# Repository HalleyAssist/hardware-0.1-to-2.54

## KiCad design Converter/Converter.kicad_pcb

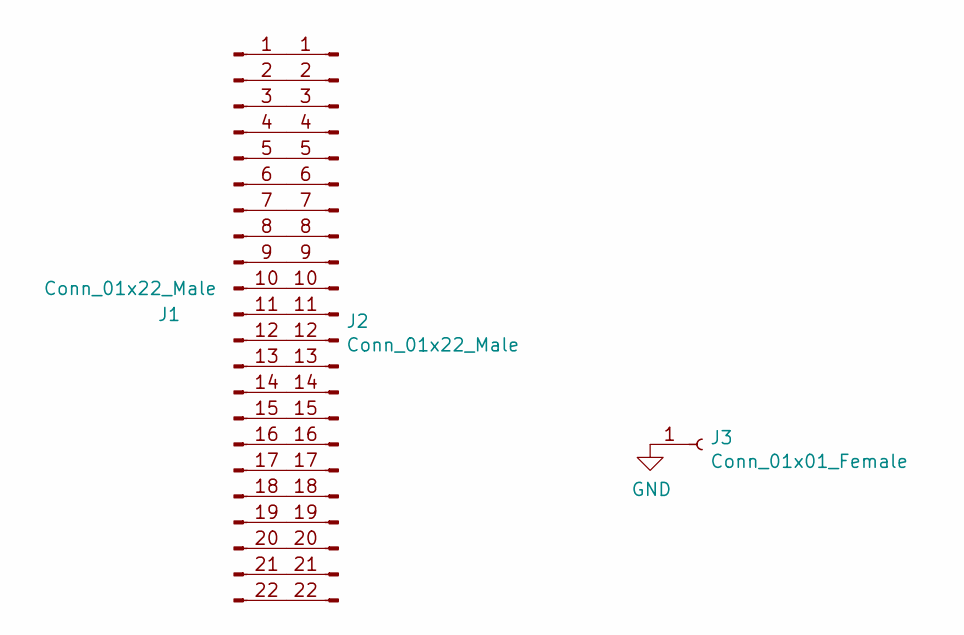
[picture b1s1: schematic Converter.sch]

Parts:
J1: Conn_01x22_Male; PinHeader_1x22_P1.00mm_Vertical
J2: Conn_01x22_Male; PinHeader_1x22_P2.54mm_Vertical
J3: Conn_01x01_Female; PinHeader_1x01_P2.54mm_Vertical

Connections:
GND: J3.1
unnamed: J1.1, J2.1
unnamed: J1.2, J2.2
unnamed: J1.3, J2.3
unnamed: J1.4, J2.4
unnamed: J1.5, J2.5
unnamed: J1.6, J2.6
unnamed: J1.7, J2.7
unnamed: J1.8, J2.8
unnamed: J1.9, J2.9
unnamed: J1.10, J2.10
unnamed: J1.11, J2.11
unnamed: J1.12, J2.12
unnamed: J1.13, J2.13
unnamed: J1.14, J2.14
unnamed: J1.15, J2.15
unnamed: J1.16, J2.16
unnamed: J1.17, J2.17
unnamed: J1.18, J2.18
unnamed: J1.19, J2.19
unnamed: J1.20, J2.20
unnamed: J1.21, J2.21
unnamed: J1.22, J2.22

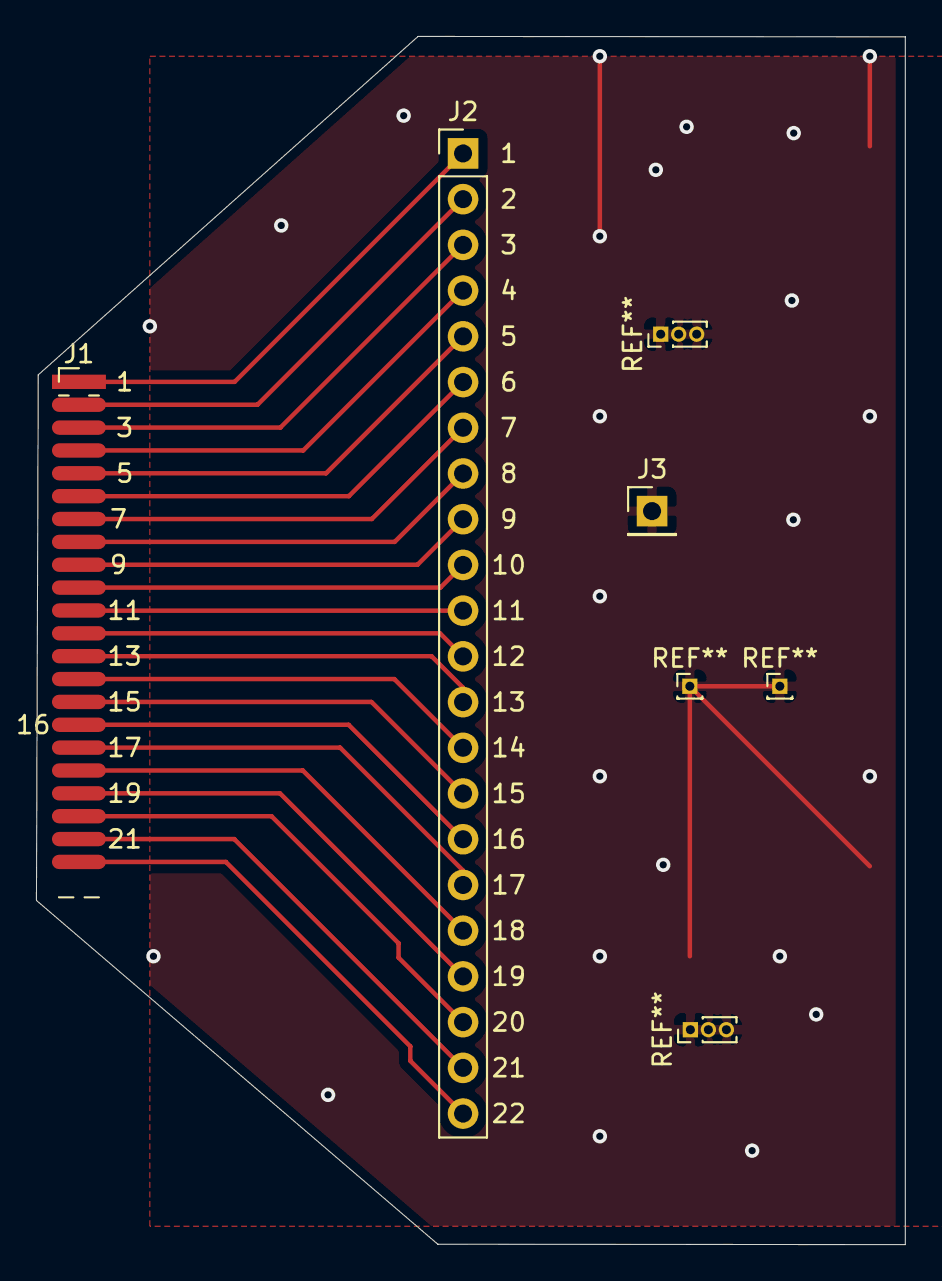
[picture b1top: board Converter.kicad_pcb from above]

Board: 2 copper layers, 48.3 x 67.1 mm, 3 parts (0 on the bottom side), 22 nets.

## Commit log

2021-07-01 simple converter pcb
